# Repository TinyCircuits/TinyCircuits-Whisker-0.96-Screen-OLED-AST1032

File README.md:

# TinyCircuits Wireling 0.96 Screen OLED
# AST1032 Rev1

The design files are located under design_files/ for the TinyCircuits AST1032 Rev 1 PCB. This is a Wireling board which features a 128x64 White Monochrome OLED display which can be controlled using the TinyCircuits TinierScreen library.

Format is in Cadsoft Eagle format - Eagle version 6.2 was used for the original design.

For more infomation on this, check out the product page at TinyCircuits.com

# License:

Design by TinyCircuits.
All design files are released under the Creative Commons Attribution Share-Alike 3.0 License, see the following link for details: http://creativecommons.org/licenses/by-sa/3.0

All text above must be included in any redistribution or derived design

This project uses designs and concepts developed as part of the Arduino project and the LilyPad project.  The TinyCircuits design files themselves (schematics, PCB and libraries) are not directly derived from these works' design files and have been created new, however the concepts and basic architecture behind the TinyDuino and TinyLily products are derived and we thank the hard work of the organizations below for their contributions to open-source hardware:
  
Original Arduino Uno Design by Team Arduino

LilyPad Arduino Design by Leah Buechley and Sparkfun Electronics

Please support the open-source hardware community

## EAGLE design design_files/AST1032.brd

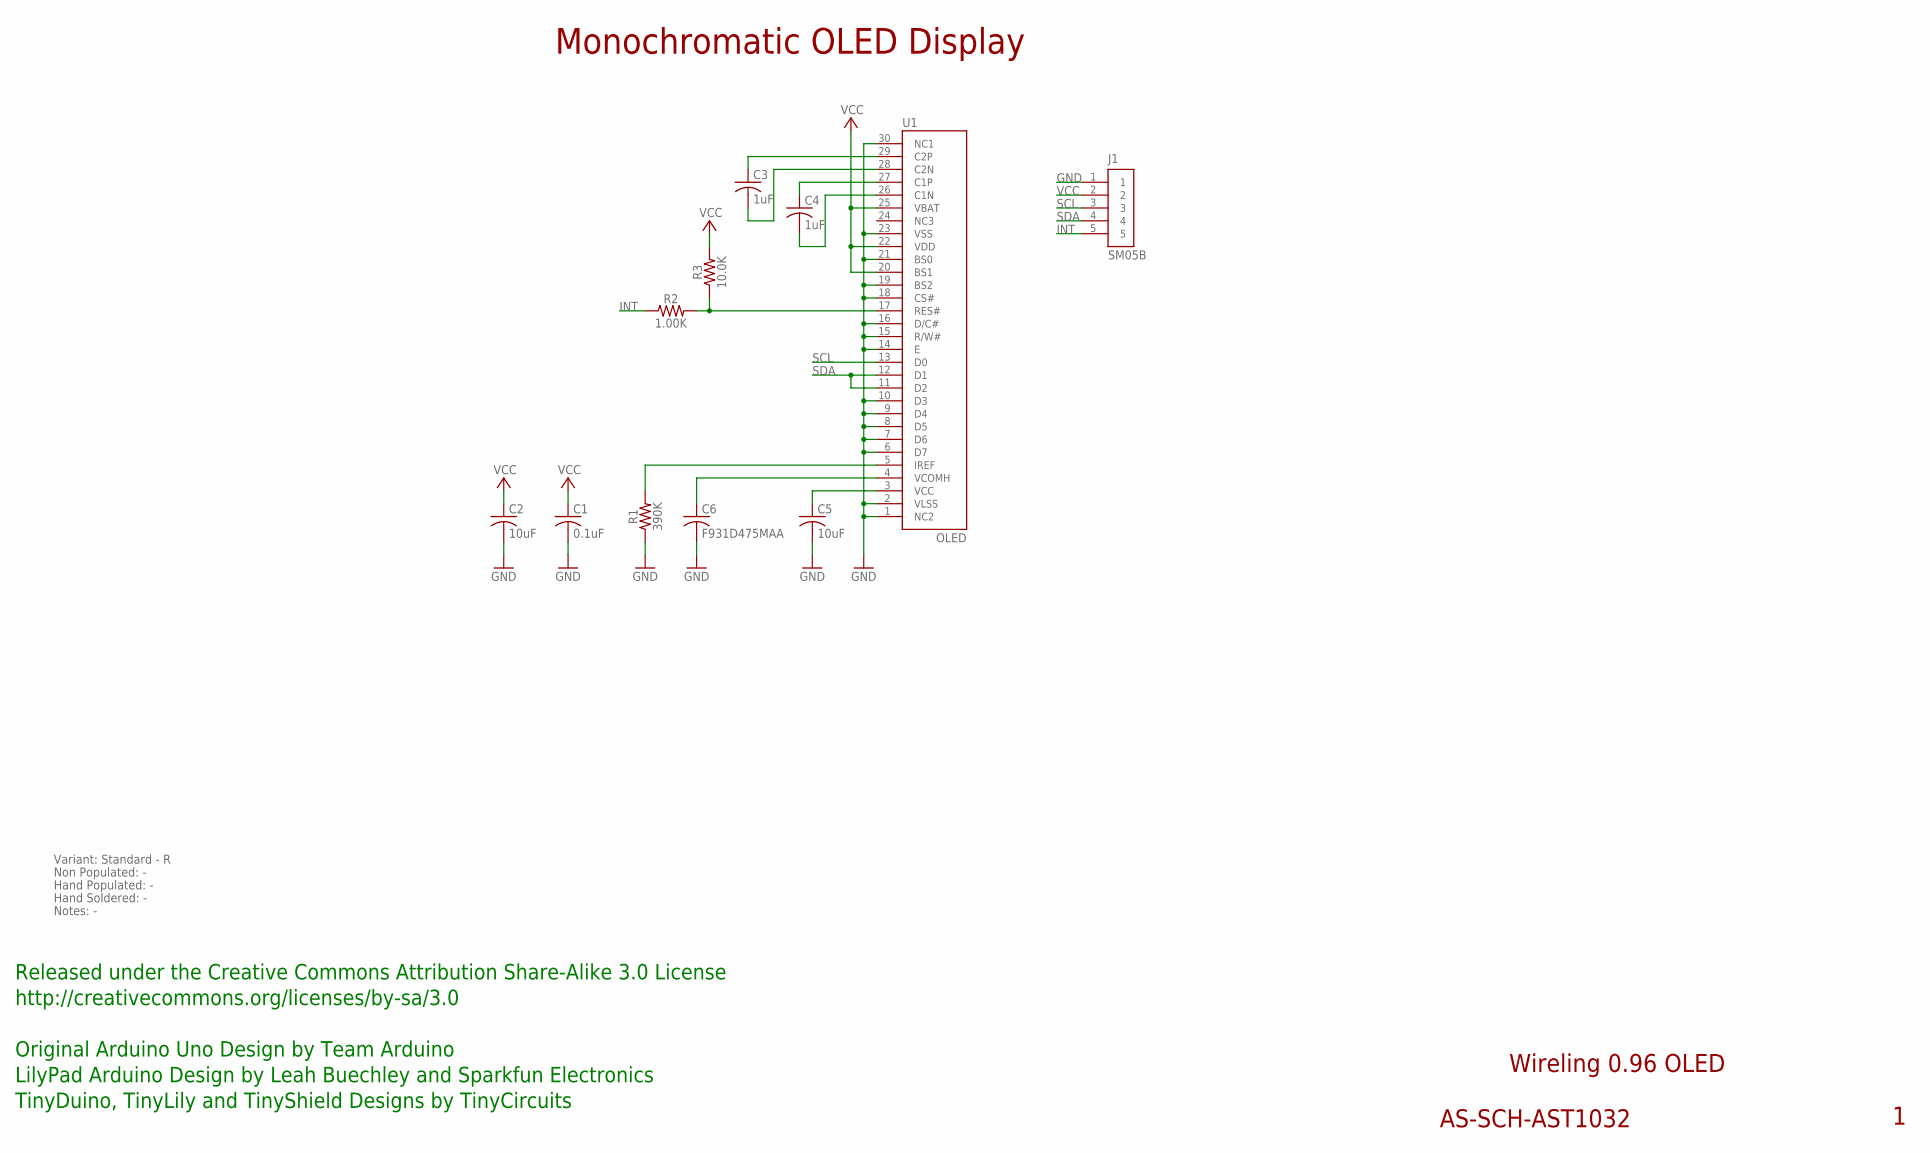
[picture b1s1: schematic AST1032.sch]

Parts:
C1: 0.1uF; C0402
C2: 10uF; C0603
C3, C4: 1uF; C0603
C5: 10uF; C0805
C6: F931D475MAA; 1206_CAP_TANT
J1: SM05B; JST_SH_5X1
R1: 390K; 0402
R2: 1.00K; 0402; PARTNO AS-ITM-00003
R3: 10.0K; 0402
U1: OLED; OLED_WHITE_30P

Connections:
GND: C1.2, C2.2, C5.2, C6.2, J1.1, R1.1, U1.1 (NC2), U1.2 (VLSS), U1.6 (D7), U1.7 (D6), U1.8 (D5), U1.9 (D4), U1.10 (D3), U1.14 (E), U1.15 (R/W#), U1.16 (D/C#), U1.18 (CS#), U1.19 (BS2), U1.21 (BS0), U1.23 (VSS), U1.30 (NC1)
INT: J1.5, R2.1
unnamed: C3.1, U1.29 (C2P)
unnamed: C3.2, U1.28 (C2N)
unnamed: C6.1, U1.4 (VCOMH)
unnamed: C4.1, U1.27 (C1P)
unnamed: C4.2, U1.26 (C1N)
unnamed: R1.2, U1.5 (IREF)
unnamed: C5.1, U1.3 (VCC)
unnamed: R2.2, R3.1, U1.17 (RES#)
SCL: J1.3, U1.13 (D0)
SDA: J1.4, U1.11 (D2), U1.12 (D1)
VCC: C1.1, C2.1, J1.2, R3.2, U1.20 (BS1), U1.22 (VDD), U1.25 (VBAT)

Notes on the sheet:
Wireling 0.96 OLED
AS-SCH-AST1032
Monochromatic OLED Display
Released under the Creative Commons Attribution Share-Alike 3.0 License
http://creativecommons.org/licenses/by-sa/3.0
Original Arduino Uno Design by Team Arduino
TinyDuino, TinyLily and TinyShield Designs by TinyCircuits
LilyPad Arduino Design by Leah Buechley and Sparkfun Electronics
Non Populated: -
Hand Populated: -
Hand Soldered: -
Variant: Standard - R
Notes: -

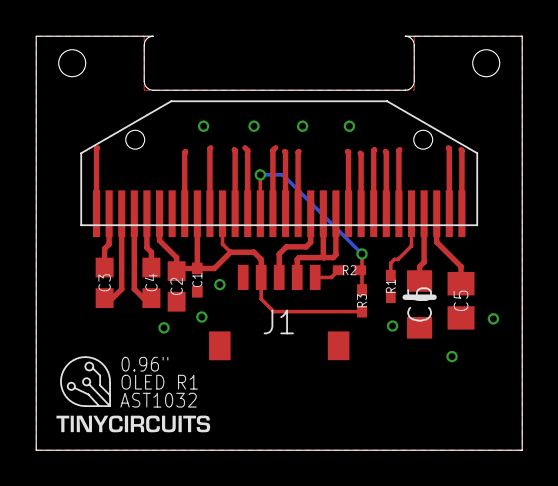
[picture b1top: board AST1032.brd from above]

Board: 2 copper layers, 27.0 x 23.0 mm, 12 parts (0 on the bottom side), 13 nets.

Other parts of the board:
U$1: DOCFIELD-TINYCIRCUITS-PCB

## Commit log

2019-09-17 datasheet
2019-12-17 updated documentation
2020-02-04 mass image update
2020-08-14 Add CAD data
